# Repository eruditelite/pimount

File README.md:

# pimount #

## Overview ##

Telescope mount driver.

## Starting Points and Connections ##

This all started with a SkyView Pro mount and Orion 7832 Dual Axis
TrueTrack Telescope Drive.  This setup works, but there are a number
of issues.

  * The battery pack is not robust.  Using rechargable D cells is
    okay, but it is not ideal for weekend trips etc.
  * There is no "guiding".  I added a port (ST4) that can be used to
    provide guiding, but haven't tried it.  Adding the ST4 port is
    described at http://www.store.shoestringastronomy.com/eq_mod.pdf .

So, this project uses a Raspberry Pi and a custom ciruit to replace
most of the 7832 drive.  The stepper motors are the only part that
isn't replaced.  It is intended to handle drive and autoguide when
complete.  The components are as follow.

  * Use a deep cycle 12 VDC battery.  This can power the Pi, stepper
    motors, other accessories, etc.  Adding a "DC to DC buck
    converter" provides 6 VDC which can be used to power the 7832 if
    desired.  Here's the result.  The paper towel roll segment holds
    the DC to DC buck converter that supplies 6 VDC as expected by
    Orion accessories.

	[Battery](https://www.dropbox.com/s/0trkuq7uk3z1awa/battery.jpg?dl=0)

  * The stepper motors use different sized connectors to avoid
    confusion.  The declination motor uses a RJ9 and the right
    ascension motor uses a RJ11.  Instead of creating a driver, I use
    a pre-made driver based on the A4988.  The version I used is the
    'ELEGOO Stepstick Stepper Motor Driver Module A4988' -- others are
    available, but KiCAD footprints must be created.  Here's how the
    wiring works.
	
  * I "reverse engineered" TrueTrack to figure out how to drive the
    stepper motors.  See appendix below...

### References ###

Others have modified the system as well. See, for example,

  * [PIC 16F627 Based EQ-5 / CG-5 Dual Axis Hand Controller]<http://telescope.marford.me.uk/Projects/PICcontroller.htm>
  * [THE EQMOD PROJECT]<http://eq-mod.sourceforge.net/>
  * [AstroEQ]<https://www.astroeq.co.uk/tutorials.php?link=custommotors>
  * [Motor]<https://www.digikey.com/catalog/en/partgroup/pm-series/536>
  * [Motor]<https://www.cloudynights.com/topic/631615-want-to-make-diy-controller-for-my-cg-4-dual-axis-motors/>
  * 

### Stepper Motor Wiring and Current Limit ###

Set the voltage (potentiometer to ground) to 125 mV.  Motor voltage
should be 10 V.

## Setup ##

## Local OLED Display ##

The plan is to use a white display with red film...

The part is IZOKEE 0.96'' I2C IIC 12864 128X64 Pixel OLED LCD Display
Shield Board Module SSD1306

First unit test... The part is IZOKEE 0.96'' I2C IIC 12864 128X64
Pixel OLED LCD Display

"The original Pi" (not sure about this, but it seems correct) used
i2c-0.  After that, i2c-1 is used (pins bcm2 and bcm3 instead of bcm0
and bcm1).  Trying to use i2c-0 is fraught with difficulties.  Using
i2c-1.

## Local Control ##

Local control uses a USB game controller (SNES style).  Don't use
iBuffalo, as there are phantom button presses!  Currently using
innext.

## Web User Interface ##

### Why ###

Allows basic control from any device with a web server.

### How ###

See https://github.com/Mjrovai/RPi-Flask-WebServer for an example
setup. That's the skeleton.

## INDI Driver ##

The most straight-forward way to support guiding seems to be with an
INDI driver.  Start with the 'drivers/telescope/telescope_simulator.*'
files in INDI.

### Install ###

Use the latest version of the INDI library by installing in /usr/local
as follows.

git clone https://github.com/indilib/indi.git
cd indi
INDI_CLONE=$(pwd)
<currently at 4543974f on master or v1.8.5>
BUILD_DIRECTORY=<wherever you want to build>
cd $BUILD_DIRECTORY
cmake --DCMAKE_INSTALL_PREFIX=/usr -DCMAKE_BUILD_TYPE=Debug $INDI_CLONE
make -j4
sudo make install

### NOTES ###

1. Use 'indiprop' to test.
   * https://github.com/aaronevers/indiprop.git
2. Adding things to the driver.
   * Add private variables in indi/pimount.h.
   * A *Vector* is required for the client to use the property.
   * For a single thing (number, string, etc.) create an array with
     one element, just creating a single element will NOT work
     (INumber ANewNumber[1], not INumber ANewNumber).

## systemd ##

As everyone uses it now...

sudo cp pimount.service /lib/systemd/system
sudo systemctl enable pimount

Then, pimount will start at boot.  Just update /usr/local/bin/pimount
and reboot to update pimount.

## Post Mortems ##

### release_1.3 ###

### release_1.2 ###

  * Circuit clean up -- the ELEGOO stepper motor pin size was too small etc.
  * Build updates.
  * Add fan control.
  * Update the board and silk screen.

### release_1.1 ###

  * I hate JST connectors!!!!!  I was finally able to make a few work,
    but it took much too long and there were too many failures (cut
    the wire and restart sort).  Is there another way?
  * Even if I stick with JST connectors, 2.0 mm is too small for the
    power connector.  The insulation doesn't fit in the crimpers.
  * I didn't measure the pins on the ELEGOO stepper motor
    drivers... They don't fit in the default through-hole size.  As I
    created the footprint, the problem would be me.  I think
    un-soldering the driver would be too hard to be reasonable.  I was
    hoping to use a socket, but with the size difference, that may be
    difficult.  At least the size of the holes should be increased!
	  * Fixed (increased the size of the holes) by
	    '4588a09 Update the ELEGOO Stepper Motor Footprint'.
  * As I'm planning on adding a fan for ventilation, there needs to be
    a fan control circuit.
  * Joystick wiring was not described adequately on the schematic.
  * Stepper moter wiring as well.
  * Not sure about the debug headers.  I didn't solder any on, but
    that pads are useful!
  * Default pin assignments are wrong.

## Issues ##

### USB Controller Only Works if Connected when the Program Starts ###

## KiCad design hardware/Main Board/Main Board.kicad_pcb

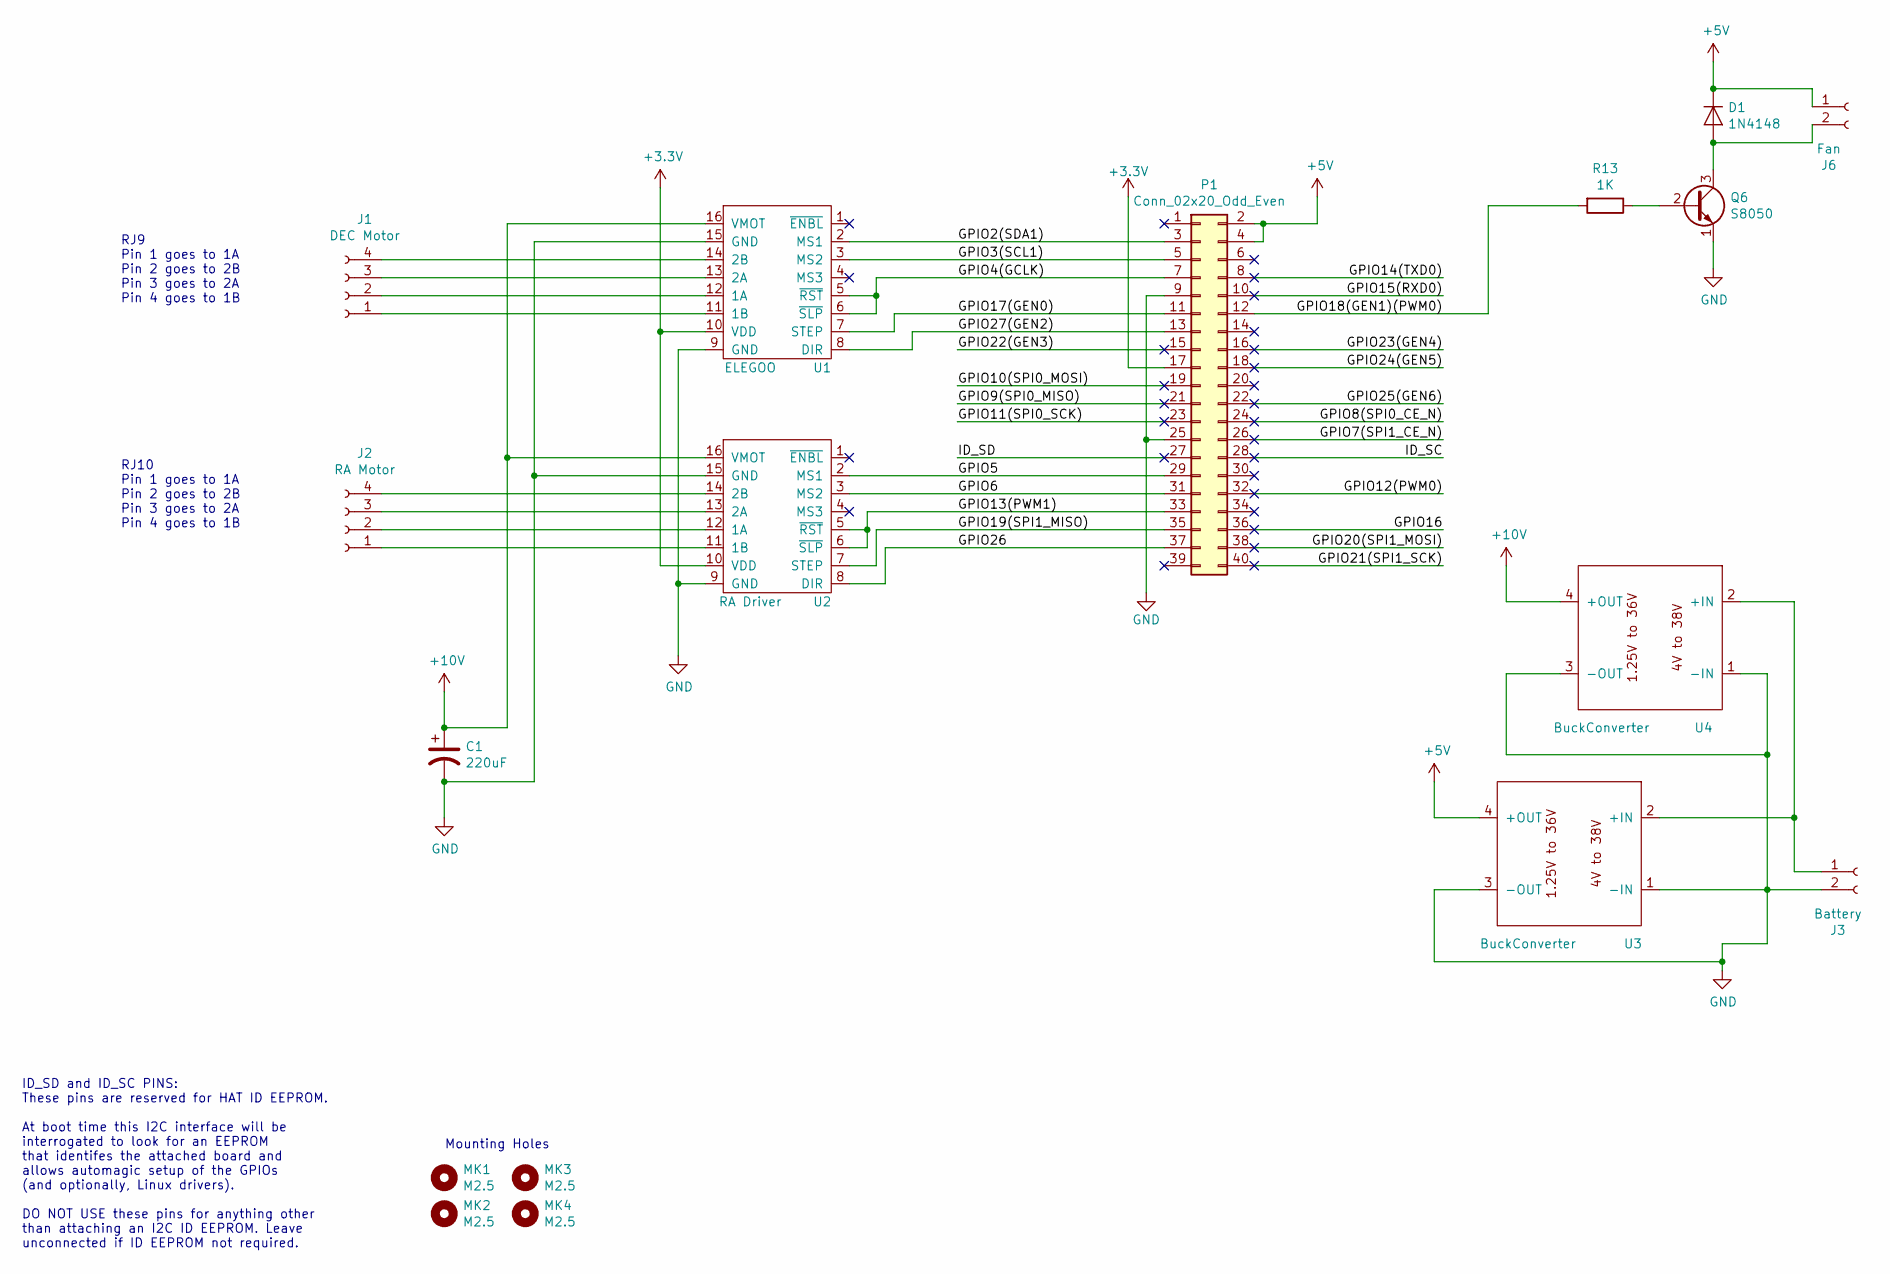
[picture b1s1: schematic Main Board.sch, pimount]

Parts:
C1: 220uF; CP_Radial_D6.3mm_P2.50mm
D1: 1N4148; D_DO-35_SOD27_P2.54mm_Vertical_KathodeUp
J1: DEC Motor; JST_PH_B4B-PH-K_1x04_P2.00mm_Vertical
J2: RA Motor; JST_PH_B4B-PH-K_1x04_P2.00mm_Vertical
J3: Battery; PhoenixContact_MCV_1,5_2-G-5.08_1x02_P5.08mm_Vertical
J6: Fan; JST_PH_B2B-PH-K_1x02_P2.00mm_Vertical
MK1, MK2, MK3, MK4: M2.5; MountingHole_2.7mm_M2.5
P1: Conn_02x20_Odd_Even; PinSocket_2x20_P2.54mm_Vertical
Q6: S8050; TO-92_Inline
R13: 1K; R_Axial_DIN0204_L3.6mm_D1.6mm_P1.90mm_Vertical
U1: ELEGOO
U2: RA Driver; ELEGOO
U3, U4: BuckConverter

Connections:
+3V3: P1.1, P1.17, U1.10 (VDD), U2.10 (VDD); also elsewhere on the board
+5V: D1.1 (K), J6.1, P1.2, P1.4, U3.4 (+OUT)
+10V: C1.1, U1.16 (VMOT), U2.16 (VMOT), U4.4 (+OUT)
/GPIO4(GCLK): P1.7, U1.5 (~RST), U1.6 (~SLP)
/GPIO5: P1.29, U2.2 (MS1)
/GPIO6: P1.31, U2.3 (MS2)
/GPIO7(SPI1_CE_N): P1.26
/GPIO8(SPI0_CE_N): P1.24
/GPIO9(SPI0_MISO): P1.21
/GPIO10(SPI0_MOSI): P1.19
/GPIO11(SPI0_SCK): P1.23
/GPIO12(PWM0): P1.32
/GPIO13(PWM1): P1.33, U2.5 (~RST), U2.6 (~SLP)
/GPIO14(TXD0): P1.8
/GPIO15(RXD0): P1.10
/GPIO16: P1.36
/GPIO17(GEN0): P1.11, U1.7 (STEP)
/GPIO18(GEN1)(PWM0): P1.12, R13.2
/GPIO19(SPI1_MISO): P1.35, U2.7 (STEP)
/GPIO20(SPI1_MOSI): P1.38
/GPIO21(SPI1_SCK): P1.40
/GPIO24(GEN5): P1.18
/GPIO25(GEN6): P1.22
/GPIO26: P1.37, U2.8 (DIR)
/GPIO27(GEN2): P1.13, U1.8 (DIR)
/ID_SC: P1.28
/ID_SD: P1.27
GND: C1.2, J3.2, P1.9, P1.25, Q6.1 (E), U1.9 (GND), U1.15 (GND), U2.9 (GND), U2.15 (GND), U3.1 (-IN), U3.3 (-OUT), U4.1 (-IN), U4.3 (-OUT); also elsewhere on the board
unnamed: D1.2 (A), J6.2, Q6.3 (C)
unnamed: J1.1, U1.11 (1B)
unnamed: J1.2, U1.12 (1A)
unnamed: J1.3, U1.13 (2A)
unnamed: J1.4, U1.14 (2B)
unnamed: J2.1, U2.11 (1B)
unnamed: J2.2, U2.12 (1A)
unnamed: J2.3, U2.13 (2A)
unnamed: J2.4, U2.14 (2B)
unnamed: J3.1, U3.2 (+IN), U4.2 (+IN)
unnamed: Q6.2 (B), R13.1

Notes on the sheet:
ID_SD and ID_SC PINS: These pins are reserved for HAT ID EEPROM. At boot time this I2C interface will be interrogated to look for an EEPROM that identifes the attached board and allows automagic setup of the GPIOs (and optionally, Linux drivers). DO NOT USE these pins for anything other than attach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
Mounting Holes
RJ9 Pin 1 goes to 1A Pin 2 goes to 2B Pin 3 goes to 2A Pin 4 goes to 1B
RJ10 Pin 1 goes to 1A Pin 2 goes to 2B Pin 3 goes to 2A Pin 4 goes to 1B

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
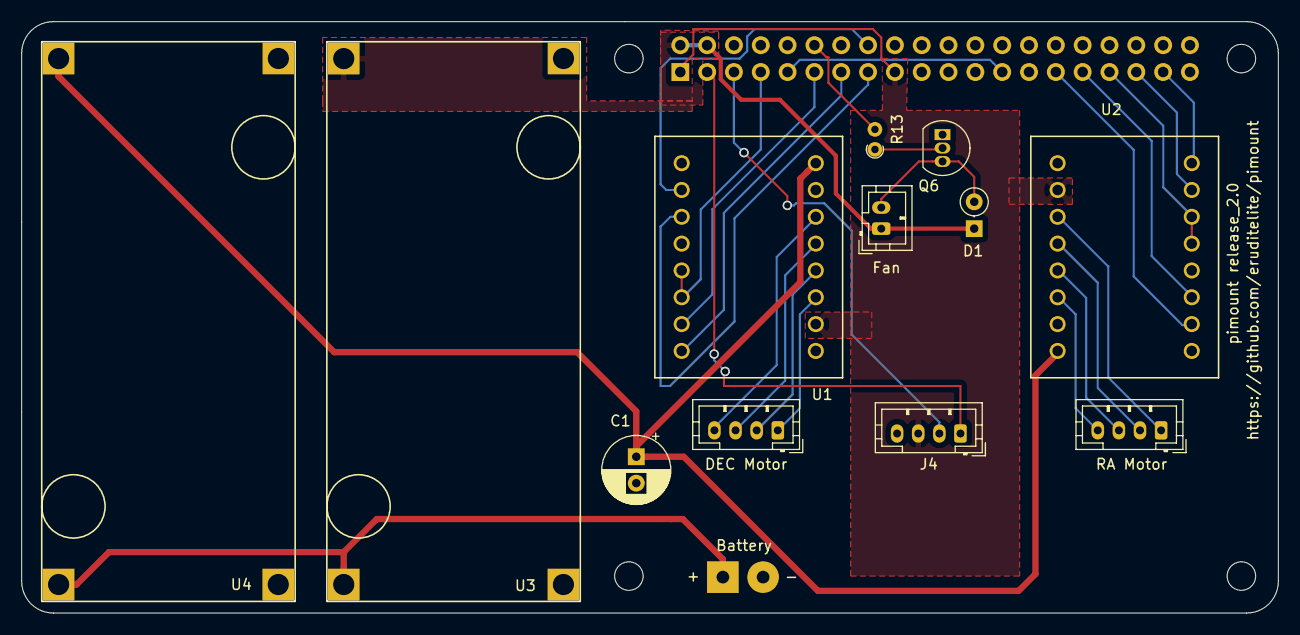
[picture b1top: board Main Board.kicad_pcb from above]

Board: 2 copper layers, 119.0 x 56.0 mm, 18 parts (1 on the bottom side), 28 nets.

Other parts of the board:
J4: OLED Display; JST_PH_B4B-PH-K_1x04_P2.00mm_Vertical

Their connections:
+3V3: J4.3; also elsewhere on the board
GND: J4.4; also elsewhere on the board

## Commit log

2018-09-02 Initial Checkin
2018-09-02 A Number of Updates...
    Add interface functions for the pigpio calls.
    Initialize the stepper drivers and buttons.
2018-09-02 No 'config' For Now
2018-09-03 compiles and runs...
2018-09-05 Buttons Control the Mount!
2018-09-08 Add a DEBUG_BUILD Option
2018-09-08 Add Tracing
2018-09-08 Clean Up Timing
2019-03-26 Add 'hardware' for Board Design
2019-03-26 First Routing...
2019-03-27 Ready to Build the Board
    release_1.0
2019-03-31 Add a Place to Keep Extra Stuff
2019-07-06 Tag and Label as Release 1.1
2019-07-06 Extended the Size of the Board
    Include space for the DC to DC converters and
    re-route.
2019-07-06 Update the ELEGOO Stepper Motor Footprint
2019-07-10 merge... main board sch
2019-07-10 Update the Circuit
    Move the input on BCM 0 to BCM 12 since BCM 0 and BCM 1
    are "special" (the "hat" standard requires and prom there).
2019-07-10 Update the Pin Number Comments
2019-07-10 Allow Pins 0 and 1
2019-07-10 Add Test Cases
2019-07-10 Reduce the "Glitch" Value
2019-07-10 Switch to README.md (from README)
2019-07-10 Add a Note about Stepper Current and Voltage
2019-07-10 Add a Fan Control Circuit
2019-07-10 Ignore pimount and Objects
2019-07-10 Add a Fan Thread
2019-07-10 Add a Glitch Option
2019-07-11 Clean up the Fan Thread
2019-07-11 Update the Pin Comments
2019-07-11 Add a Web UI
2019-11-11 Add a Control Interface
2019-11-11 A Shell Script with the Right Pin Numbers
2019-11-11 Updates for release_1.2
2019-11-11 Remove All Objects
2019-11-13 Add a Input (Joystick) Test
2019-11-15 Switch from 'pigpiod_if2' back to 'pigpio'
    Using the daemon seems like a great idea, it would even
    allow the controller to run on a different host! BUT,
    the latency of the joystick is too high. So, instead of
    using the daemon, work directly and use interrupts for
    the buttons instead of callbacks.
2019-11-15 Add a 'cscope' Target
2019-11-15 Performance Updates
2019-12-18 Captures of the Orion TrueTrack
    And scripts to graph them.
2019-12-20 Fix a Defect Using pthread_cond_timedwait
    pthread_cond_timedwait expects CLOCK_REALTIME instead of
    CLOCK_MONOTONIC. It also wants a time, not a length of
    time, to wait for.
2019-12-20 Fix a Compiler Warning
2019-12-20 Add a Read Function
2019-12-23 Add a Test for the Output Drivers
    Note that this changes the a4988 interface by adding a
    parameter to a4988_step(), the width of the pulse.
2019-12-23 Add the 'tests' Directory to All Targets
2019-12-26 Fix a Typo
2019-12-26 Add References to Other Projects
2019-12-31 Add Signal Handling and Infinite Stepping
2020-01-03 Add a Line for RA Tracking in output.sh
2020-01-10 Add Fan On and Off Scripts
2020-01-10 Update the Tracking Parameters (tested using the Moon)
2020-01-14 Use the 'timespec' Functions from timespec_mod
2020-01-15 Now that Width is right, Fix Delay...
    Just tests/output.c for now.
2020-01-15 Clean Up Warnings
2020-01-15 Update CFLAGS and Fix Warnings
2020-01-15 Updated RA Tracking Test
    See tests/output.sh... After cleaning up the timing
    and delay, make output match the old settings.
2020-01-16 Update the Main Program...
    Handle the new timing corrections, and RA tracking.
2020-01-20 Clean Up Cscope Files
2020-02-13 Add an INDI Driver
2020-02-13 Clean up Control
    Check for failures when using sockets, and add the port as
    a parameter to pimount, and tests/control.
2020-02-13 Set Thread Priorities
    For threads where time is of the essence, increase the priority.
2020-02-19 Update Socket Handling in Control
2020-03-18 Add a Number Array Property to the INDI Driver
2020-03-19 README Updates for INDI
2020-03-22 Add INDI Notes
    Describe adding properties.
2020-03-23 Add a New INDI Property
2020-04-20 Update the Motor Control
    Instead of specifying the low-level stepper motor parameters,
    just indicate the axis (RA or DEC), direction, and rate in
    arcseconds per sec.
    This should make working with the INDI Guider interface easier...
2020-04-22 Use a USB Controller Instead of a Custom Controller
2020-04-30 Remove the Joystick Circuitry and Cleanup
2020-06-29 Major Code Cleanup
2020-07-13 Updated to KiCAD 5.1.6 and Fixed Warnings
    The edge cuts weren't joined perfectly -- apparently 5.1
    checks for this!
2020-07-18 Cleanup Locking/Unlocking
    As everything is fairly simple, locking should always work. Instead
    of handling this in multiple places, create lock()/unlock() functions
    that simply exit the application if there is an error getting/freeing
    the lock.
2020-07-23 Make the Global State Avaialble Everywhere
    Just make sure to use the lock!
2020-07-28 Update Software to Match the New Board
    The main changes are
    -1- Change the GPIO pin numbers for DEC.
    -2- Add the OLED status indicator.
2020-07-28 Indicate the wattage of R13.
2020-07-31 Update Help and Command Line Parsing
    For the rate test application...
2020-07-31 Cleanup Comment Grammer
2020-07-31 Update Button Definitions
    As the iBuffalo controller adds phantom button presses,
    switch to innext (still SNES USB).
2020-07-31 Latest Buttons and Rate Calculations
2020-08-02 Add a Section for Issues
2020-08-15 Update the use of INDI
    Add install instructions to README.md and use pkg-config
    for the include and library paths.
2020-08-15 Update Descriptions and SystemD
2020-08-15 Rename the INDI Driver Connector
    Change the name of the INDI driver connector to pimount-indi.
2020-08-15 Add an 'install' Target
    This installs the binaries in /usr/local and adds systemd
    services for pimount and pimount-indi
2020-08-15 Add a SystemD Service for the INDI Driver Connector
2020-08-15 Add a Systemd Service File and Describe Usage
2020-08-15 Add Dependencies (Except indi)
2020-12-15 Update the 'install' Target
    Stop services, and restart them after, as needed.
2020-12-15 INDI Class Update
    ** incomplete **
2023-02-05 hardware: Latest KiCAD Changes
2023-02-05 tests: Clean 'status' in GNUMakefile
2023-02-05 pimount: Make it Easier to Adjust Speed
    Define the RA speed for tracking in one place.
2023-08-23 Initial Commit for a Custom Mount
